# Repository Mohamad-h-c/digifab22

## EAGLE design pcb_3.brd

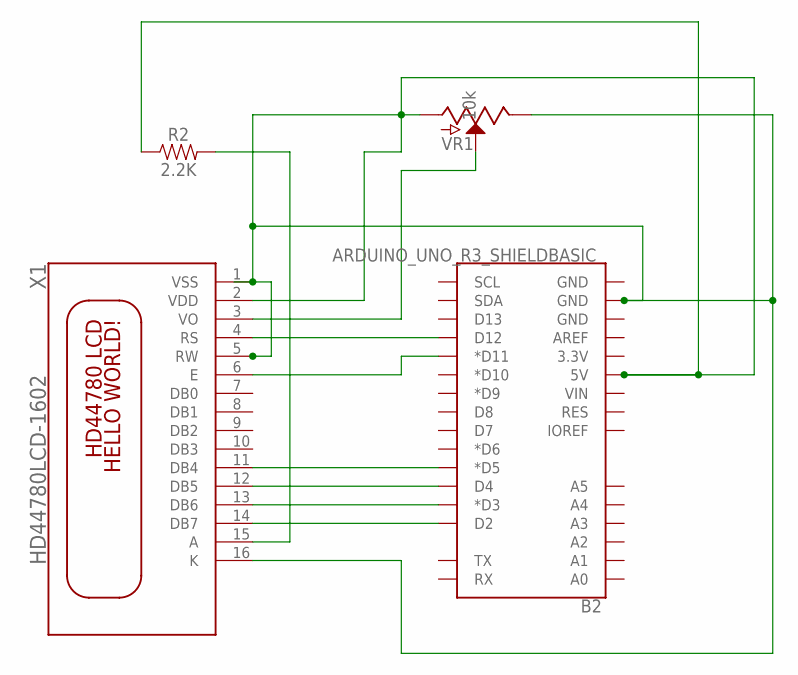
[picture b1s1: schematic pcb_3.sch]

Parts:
B2: ARDUINO_UNO_R3_SHIELDBASIC; UNO_R3_SHIELD
R2: 2.2K; 0402
VR1: 10k; POT-PTH-ALPS-KIT
X1: HD44780LCD-1602; LCD1602

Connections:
unnamed: B2.D2, X1.14 (DB7)
unnamed: B2.D3 (*D3), X1.13 (DB6)
unnamed: B2.D4, X1.12 (DB5)
unnamed: B2.D11 (*D11), X1.6 (E)
unnamed: B2.D12, X1.4 (RS)
unnamed: VR1.P$2 (S), X1.3 (VO)
unnamed: B2.D5 (*D5), X1.11 (DB4)
unnamed: R2.2, X1.15 (A)
VDD: B2.5V, B2.GND@1 (GND), R2.1, VR1.P$1 (E), VR1.P$3 (A), X1.1 (VSS), X1.2 (VDD), X1.5 (RW), X1.16 (K)

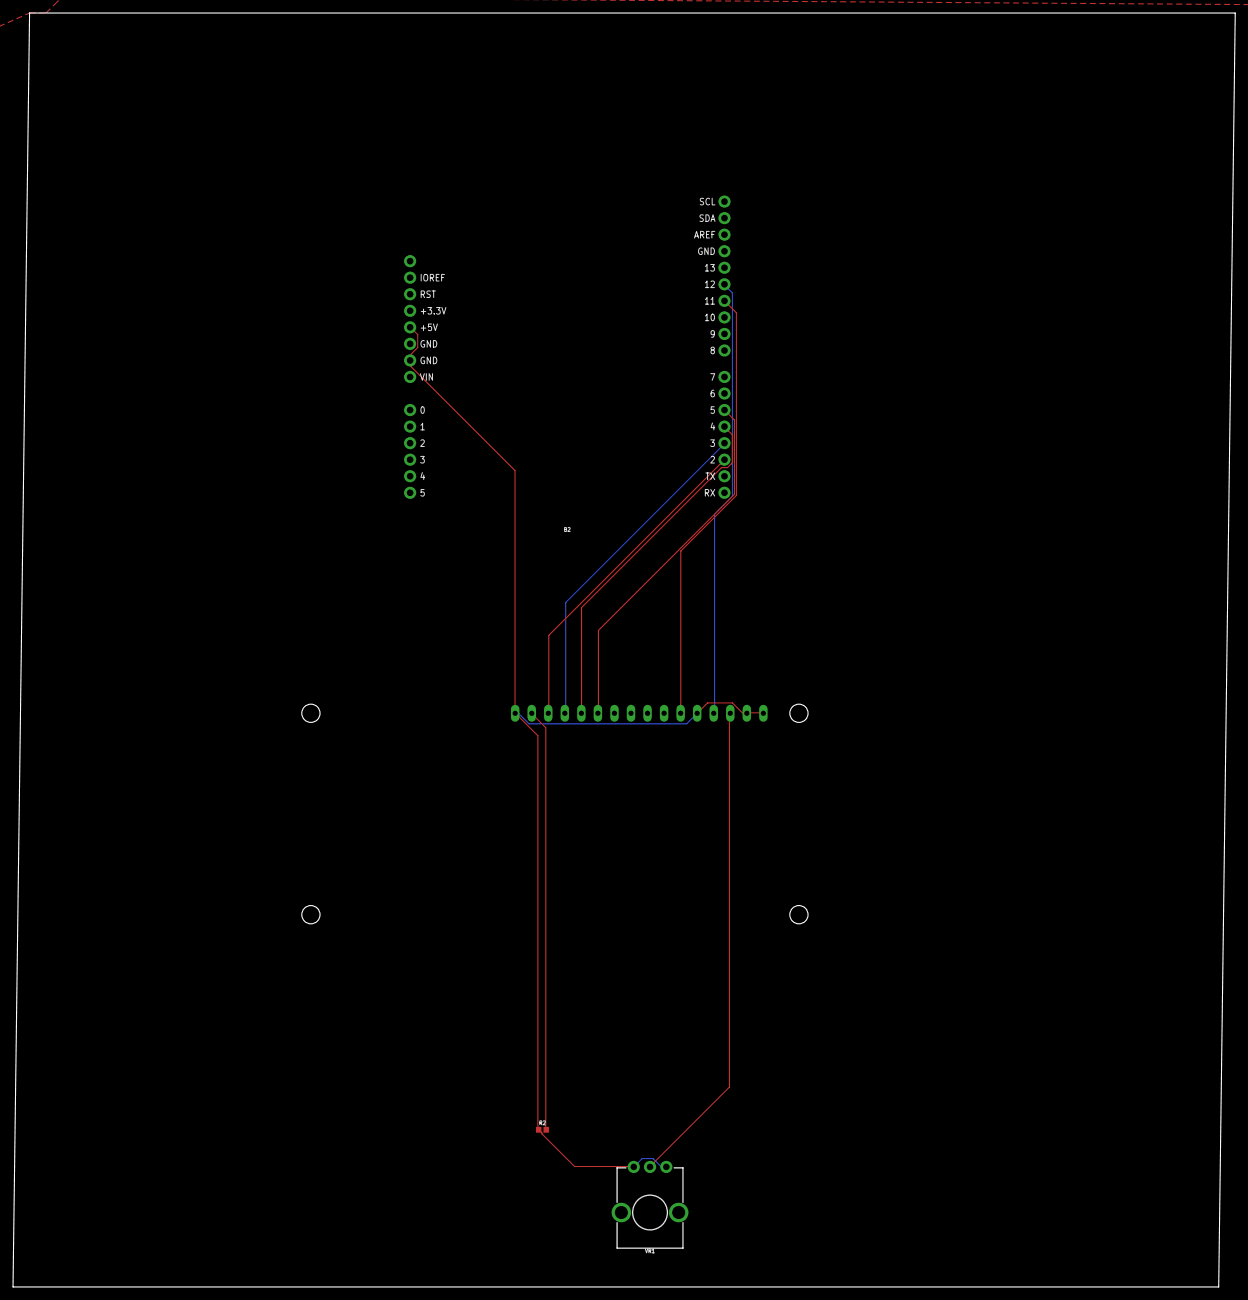
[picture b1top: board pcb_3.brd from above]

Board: 2 copper layers, 187.6 x 195.6 mm, 4 parts (1 on the bottom side), 9 nets.

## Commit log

2022-09-26 ttt
    test chamsi
2022-09-26 bytte navn
    en
2022-09-27 info
    litt om meg
2022-09-27 info2
    info
2022-09-27 bilde4
    bilde
2022-09-27 post
    epost
2022-09-27 hiof
    logo
2022-09-27 logo
    image
2022-09-27 rettfeil
    rett feil
2022-09-30 innledning
    litt om oblig
2022-09-30 beskrivelse
    beskrevlse om oppgave og hva er den.
2022-09-30 beskrivelse om projekt11
    litt om projekt1
2022-09-30 test
    test1
2022-09-30 icon
    pro1
2022-09-30 test2
    endring
2022-09-30 endrin 4
2022-09-30 test6
2022-09-30 test7
2022-09-30 test 9
2022-09-30 ending
2022-10-24 O
    BYT
2022-10-24 NEW
    NEW_1
2022-10-24 UPTADING_2
    new_2
2022-10-24 w
    wj
2022-10-24 asdasd
    asdasdasd
2022-10-24 aq
    aq
2022-10-24 22222
    22222
2022-10-24 text
    t1
2022-10-24 endring test
    endring
2022-10-24 se mer
    mer
2022-10-24 t2
    t22
2022-10-24 2
    3
2022-10-24 Litt om oblig1
    o
2022-10-24 BILDE
    B
2022-10-24 Bilde
    bilde
2022-11-18 OBLIG
    EN
2022-11-18 OB2
    1
2022-11-18 3te
    overskrift
2022-11-18 se mer
    ob2
2022-11-18 t4
    t4,
2022-11-18 bilde
    1test
2022-11-18 bilde 2
    bilde 2
2022-11-18 bilde4
    b4
2022-11-18 bilde 5
    5
2022-11-18 bilde 6
    b6
2022-11-18 na
    b8
2022-11-18 p2
    pro2
2022-11-18 bil1
    1+2+3
2022-11-18 dbil
2022-11-19 edit
    1
2022-11-19 bde
    1
2022-11-19 bilde
2022-11-19 delet
    sd
2022-11-20 bilder
    1t
2022-11-20 komtar
    kommant
2022-11-20 desigen bilder
    desigen
2022-11-20 delet
2022-11-20 bilder
    bilder
2022-11-20 bilde
    c
2022-11-20 endring i logo
    bil44
2022-11-20 endre 3
    endre3
2023-02-05 add
    add bilde
2023-02-05 add bilde 2
    add
2023-02-05 png
    pnga
2023-02-05 klik
    bilde
2023-02-05 add bildr
    add bilde t
2023-02-05 3
    add projekt3 bilde
2023-02-05 boblig 3
    bilde
2023-02-05 p
    projekt3
2023-02-05 beskrevelse
    1
2023-02-05 ligge bilder til ar
    3
2023-02-05 VI
    V
2023-02-05 youtube
    v
2023-02-11 forklaring
    2
2023-02-11 beskriver av 2p
    1
2023-02-15 endring
    15.05
2023-02-15 slett
    sleet buttom
2023-02-15 delet all buttom
    delet
2023-02-16 Code SGP30 sensor ,reads the baseline values for CO2 prints them to the Serial Monitor
2023-03-12 oblig4
    ny sec
2023-03-12 undo
    tilbak
2023-03-12 pcb
    bilde
2023-03-12 PNG
    PNG
2023-03-12 BILDE3
    PCB
2023-03-12 p
    p1
2023-03-19 KORT OM PROJEKT
    beskrivelse
2023-03-19 Schematic
    sc
2023-03-19 bes
    b
2023-03-19 Bord
    bord
2023-03-19 slett
    slett
2023-03-19 stor bilde
    s
2023-03-19 png
    s
2023-03-19 b
    b
2023-03-19 x
    x
2023-03-23 levering
    l
2023-05-21 Create Slutt_Prosjekt
2023-05-23 Endring
    E1
2023-05-23 bilder
    flere bilder
2023-05-23 pr1
    pr1
2023-05-23 bildere
    pr3
2023-05-23 pr4
    og 5
2023-05-23 pr6
    7.8.
2023-05-23 png
    pr6
2023-05-23 pr9
    9,10,11
2023-05-23 png
    p
2023-05-23 bilde
    p
2023-05-23 p
    p
2023-05-23 v
    v
2023-05-23 a33
    a
2023-05-23 delet
    d
2023-05-23 om meg
    ommeg

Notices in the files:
parts and their libraries:
SparkFun-Boards: Licensing: Creative Commons ShareAlike 4.0 International - https://creativecommons.org/licenses/by-sa/4.0
